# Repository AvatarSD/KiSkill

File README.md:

# KiSkill — agent skills for KiCad

**Give your coding agent full, headless control of any KiCad project.**
KiSkill is a pack of [Claude Code](https://claude.com/claude-code) skills plus
a pure-Python engine (`kx`) that lets an agent read, edit, verify, review, and
fabricate KiCad schematics and PCBs — no GUI, no mouse, every change checked
before it lands.

Built on a lossless s-expression parser (byte-identical round-trips on real
2 MB boards), a geometric verifier that runs before every write, and visual
diffs fed back to the agent so it can *see* what it changed.

> Targets KiCad 9/10 (file-based), plus LIVE board editing in an open KiCad 10
> PCB editor over IPC (`kx live pcb`, also on a remote host via an ssh socket
> forward); live schematic editing rides the same adapter on KiCad 11. On
> KiCad 10 a GENERATED schematic updates in the operator's open editor
> (`kx live sch regen`: save, regenerate, revert through the editor window). The core
> engine is stdlib-only; live mode needs `kicad-python` in the repo `.venv`
> (`python3 -m venv .venv && .venv/bin/pip install kicad-python==0.8.0`).

---

## Install

**Tell your agent** (Claude Code, or any agent that reads `~/.claude/skills/`):

> Clone https://github.com/AvatarSD/KiSkill and run its `install.sh` to set up
> the KiCad skills, then verify with `kx root`.

**Or do it yourself** — one clone, one script, no pip:

```bash
git clone https://github.com/AvatarSD/KiSkill.git
cd KiSkill
./install.sh          # symlinks skills → ~/.claude/skills, kx → ~/.local/bin
```

`install.sh` is idempotent (re-run after `git pull`) and reversible
(`./install.sh --uninstall`). The engine is pure Python stdlib, so there's
nothing to compile. KiCad itself (for ERC / render / fab) is resolved
automatically: native `kicad-cli` on PATH first, then the `org.kicad.KiCad`
flatpak, then the nightly. Override with `KX_KICAD_CLI` — e.g. set it to
`kicad-cli-nightly` when you edit with the v11 nightly, so verification
evidence comes from the same engine that writes your files.

Then just ask:

> *"Use the kicad-project skill to open `~/boards/widget/widget.kicad_pro`,
> add a 3V3 LDO block to the schematic, and show me a diff."*

---

## The skills

| skill              | what it does |
|--------------------|--------------|
| **kicad-project**  | Session state machine (CLEAN→PROBED→…→COMMITTED), backend/lock detection, lib tables, git hygiene. Start here. |
| **kicad-component**| Find parts in local + official libs; fetch missing ones (LCSC via easyeda2kicad, SnapEDA/UltraLibrarian zips); register lib tables. |
| **kicad-schematic**| Generate & edit `.kicad_sch`/`.kicad_pcb` programmatically with a geometric verifier, headless ERC, and rendered visual checks. |
| **kicad-pcb**      | Stage footprints so *Update-PCB-from-Schematic* adopts them without dupes; probe geometry; run DRC; render layers. |
| **kicad-layout**   | Schematic → placed + routed board via freerouting (DSN/SES loop), gated on DRC. |
| **kicad-review**   | Pixel diff, semantic tree diff, ERC/DRC set-diff vs a baseline, and a forum-distilled rule canon. Run before every commit. |
| **kicad-fab**      | Grouped engineering BOM, JLCPCB BOM + CPL, gerbers, drill — ready for the fab house. |
| **kicad-emsim**    | Electromagnetic field sim via gerber2ems + openEMS (dockerized): S-parameters, impedance, E-field PNGs. |
| **kicad-improve**  | Self-improvement loop: each tick researches forums, tests against fixtures, and folds lessons back into the skills. |

Every skill is one self-contained `SKILL.md`. The shared engine lives in
`kicad_lib/` and is reachable from anywhere via the `kx` CLI (`kx root` prints
the repo so skills stay portable no matter where you cloned).

## Why it's safe to let an agent drive

- **Lossless parser** — token-equal round-trips proven on multi-MB boards;
  byte-identical for `.kicad_sch`/`.kicad_sym`/`.kicad_mod`.
- **Verify-before-write** — a geometric verifier (pins, overlaps, grid) must
  pass before any file is saved; nothing commits until a review diff is judged.
- **Evidence, not vibes** — renders and triple diffs flow back to the agent so
  decisions are made on what actually changed.

See [`doc/DESIGN.md`](doc/DESIGN.md) for the architecture, state machine, and
the distilled schematic rule canon.

## Requirements

- Python 3.10+ (engine is stdlib-only).
- KiCad 9 or 10 — native or flatpak (auto-resolved; `KX_KICAD_CLI` to pin) —
  for ERC, rendering, and fab output. Pure file parsing/editing works
  without it.
- Optional per-skill: `cairosvg`/Pillow (render crops), Docker (emsim),
  a bundled freerouting jar (layout).

## Contributing

Issues, fixtures, and PRs welcome — especially real-world boards that stress
the parser and forum-sourced rules worth encoding. Start with
[CONTRIBUTING.md](CONTRIBUTING.md) and the open items in
[`doc/BACKLOG.md`](doc/BACKLOG.md). The `kicad-improve` skill is itself a
working example of how the pack grows.

## License

[MIT](LICENSE) © KiSkill contributors.

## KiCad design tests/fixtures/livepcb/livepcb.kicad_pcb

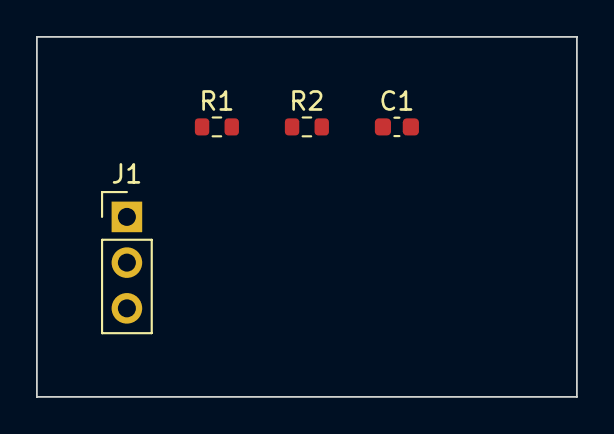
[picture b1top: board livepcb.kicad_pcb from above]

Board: 2 copper layers, 30.0 x 20.0 mm, 4 parts (0 on the bottom side), 3 nets, no tracks yet.

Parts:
C1: 100n; C_0603_1608Metric
J1: IN; PinHeader_1x03_P2.54mm_Vertical
R1, R2: 10k; R_0603_1608Metric

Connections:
GND: C1.2, J1.3, R2.2
OUT: C1.1, J1.2, R1.2, R2.1
VIN: J1.1, R1.1

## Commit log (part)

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2026-06-10 docs: architecture, state machine, atomic ops, rule canon
2026-06-10 feat: lossless sexp parser + round-trip soak test (token-equal on 2.3MB pcb)
2026-06-10 feat: kx CLI — probe (structured schematic inventory) + check
2026-06-10 feat: skill pack v1 — project/component/review/improve + evolved schematic skill + backlog
2026-06-10 fix(skills): subagent-found gaps - flatpak-safe scratch path, lock-file tilde note, deferred-tool note, round-trip claim precision
2026-06-10 docs: tick backlog (geom/verify ported); point skill at kicad_lib.verify
2026-06-10 feat: geom.py — grid snap, rot_xy/mirror, pin world position
2026-06-10 feat: verify.py — geometric verifier (rules 1-6) + mutation tests (8/8 caught)
2026-06-10 fix(verify): coincident pin stacks count as one junction item (eeschema draws no junction at pin-on-pin)
2026-06-10 feat: testproj fixture — generated opamp-follower sheet, verifier-gated, ERC 0/0, visually reviewed
2026-06-10 docs: tick backlog (testproj); skill lesson — place and tie off unused multi-unit opamps
2026-06-10 refactor: gen_testproj drives kicad_lib.ops; test_ops with regen probe-equal gate (caught dropped R2)
2026-06-10 docs: tick backlog (atomic ops at lib level; CLI surface follow-up)
2026-06-10 feat: build.py node builders + ops.py atomic document ops (place/wire/label/junction/set_prop/delete)
2026-06-10 feat: diff.py triple diff (pixel/semantic/ERC) + kx diff REV FILE; alpha-flatten fix for transparent renders
2026-06-10 docs: tick backlog (diff.py); kicad-review skill points at kx diff + transparency gotcha
2026-06-10 feat(sexp): eeschema pts xy-grouping — byte-identical sch/sym/mod round-trip, gated in tests
2026-06-10 fix: regenerate testproj fixture with byte-stable formatter (gate caught stale pts layout)
2026-06-10 feat: component index — sqlite FTS5 over 222 official libs, kx index/find, extends-inheritance
2026-06-10 feat: source.py — kx fetch (easyeda2kicad, live-tested C25804) + import-zip + lib-table registration; sexp order-preservation fix for third-party files
2026-06-10 feat: live.py backend adapter + kx env (locks, IPC socket probe incl. flatpak path, kipy via venv)
2026-06-11 feat: pcb.py footprint staging + kicad-pcb skill (netlist link, uuid refresh, donor empty board)
2026-06-11 feat: fab.py + kicad-fab skill — grouped BOM, JLC BOM/CPL, gerbers+drill via kx fab
2026-06-11 feat: layout.py headless autoroute chain (pcbnew DSN/SES + bundled freerouting) + kicad-layout skill
2026-06-11 feat: emsim.py (gerber2ems+openEMS docker runner, stackup translation) + kicad-emsim skill
2026-06-11 fix(emsim): synthesize default 2-layer FR-4 stackup when board has no (stackup) section
2026-06-11 fix(emsim): mount sim dir at subpath - mounting over /home/docker shadowed the image toolchain
2026-06-11 test+docs: emsim prepare() tests; chain validated via meander_loose smoke (physical S11, 455ps delay)
2026-06-11 fix: e2e sweep #2 — kx wrapper on PATH, nightly-aware env detection, freerouting version glob, donor override, 12 skill-doc gaps closed
2026-06-11 fix(live): real nightly detection — wrapper CLI, 10.99→v11 major, ApiError-tolerant ping, open_documents()
2026-06-11 feat(live): schematic IPC validated on nightly 10.99 — kipy-master bootstrap (protoc+protol+.pth), live read/create/commit/remove e2e test, handler-gap map
2026-06-11 docs(skills): live-IPC editing pattern + handler map into kicad-schematic/kicad-project/DESIGN; env-aware recommended-backend test
2026-06-11 feat(live): kx live — verified atomic ops on the running schematic (wire/junction/label/text/rm, net-blind verifier gate, refusal=no-commit)
2026-06-11 docs(skills): kx live command surface + net-blind gate scope into kicad-schematic; backlog tick
2026-06-11 chore: untrack stray __pycache__
2026-06-11 feat(sexp): .kicad_pcb byte-fidelity — pcb pts dialect (≤5 inline, 4/line chunks) + prettifier token wrap at col 72; real-board soak gate in test_roundtrip
2026-06-11 docs: byte-fidelity now covers pcb — skill warning lifted, backlog tick
2026-06-11 feat(cli): kx power-audit — PWR_FLAG/rail driver sanity from probe; test locks the netlist-drops-PWR_FLAG gotcha (ERC sees it, netlist blind)
2026-06-11 docs(skills): power_pin_not_driven fix recipe + netlist-blind gotcha into kicad-schematic/kicad-review; forum-sweep 1 logged
2026-06-11 feat(cli): kx unit-audit — multi-unit part completeness from the schematic
    Forum sweep 2 (kicad.info unused-pin threads + KLC S4.5): every unit of a
    multi-unit part (dual/quad opamp, gate pack) must be placed, and a spare
    unit still has to be tied off — KiCad ERC raises missing_unit /
    missing_input_pin otherwise. The testproj MCP6002 is a dual opamp (units
    A/B/power, all placed), so the lesson is lockable cold from the existing
    fixture with zero new fixtures.
2026-06-11 docs(skills): multi-unit completeness recipe + kx unit-audit into kicad-schematic/kicad-review; forum-sweep 2 logged
    Deepen the thin missing_unit one-liner in both skills into a recipe: place
    every unit, tie off spares, kx unit-audit front-runs ERC. Log forum-sweep 2
    and the no-connect-discipline candidate for the next sweep.
2026-06-11 test(nc): lock no_connect_connected — NC flag on a live node is an ERC error
    Forum sweep 3 (kicad.info t/46229, t/21294): a No-Connect flag means
    "nothing else attaches here". The inverse trap — a NC flag on a pin/node
    that IS connected — raises `no_connect_connected` (underscores; verified
    empirically, not assumed). Lock it cold from the existing fixture: the clean
    testproj has zero NC markers and no such code; inject one NC on a live
    junction (>=3 segments meet there, so it is unambiguously connected) and the
2026-06-11 docs(skills): no-connect-flag discipline into kicad-schematic/kicad-review; forum-sweep 3 logged
    Both directions: add a NC flag to a genuinely-unused pin to silence
    pin_not_connected (document intent, don't lower severity); the inverse trap
    no_connect_connected = a NC flag on a wired node (delete flag or wire, not
    both). Log sweep 3 and queue reference annotation/uniqueness as the next
    unblocked candidate (completes the power/unit/reference pre-flight trio).
2026-06-11 feat(cli): kx ref-audit — reference uniqueness/annotation (ERC is blind to it)
    Forum sweep 4 (kicad.info t/32585 + Annotation docs) completes the
    power/unit/reference pre-flight trio. PROVEN gotcha (not assumed): kicad-cli
    sch erc --severity-all reports 0/0 for both a duplicate designator (two R1)
    and an unannotated one (R?) — duplicate-ref and annotation are Annotation-
    tool checks (SCH_REFERENCE_LIST), NOT ERC violations. A headless ERC pass
    stays green while two R1s cross-merge in the netlist. Parallel to the
2026-06-11 docs(skills): ERC is blind to dup/unannotated refs + kx ref-audit; forum-sweep 4 logged
    Add the proven gotcha (kicad-cli sch erc does NOT catch duplicate or
    unannotated designators — annotation-tool checks, not ERC) to kicad-schematic
    §7 and a new "what headless ERC does NOT catch" block in kicad-review, both
    pointing at kx ref-audit. Log sweep 4 (pre-flight trio complete) and queue
    default-disabled ERC checks (the .rpt "Ignored checks" footer) as next.
2026-06-11 docs(backlog): reliability gap audit — 9 prioritized items from code analysis
    Audit of kicad_lib + kx + skills for what blocks RELIABLE agent edits:
    1. verify() never runs against the file on disk (only live_ops/tests) —
    netmodel extraction is the keystone item; unblocks the sweep-3 NC
    audit and 'netlist == intent'.
    2. No kx write-op CLI — file edits lack the live_ops refusal contract.
    3. flatpak invocation hardcoded in diff/fab/pcb/emsim + index OFFICIAL
2026-06-11 feat(kcli): one kicad-cli resolver — evidence engine must match editing engine
    Found live: user edits with the native v11 nightly while diff/fab/pcb/
    live each hardcoded the flatpak KiCad 10 — ERC/render/netlist evidence
    came from a DIFFERENT engine than the one writing the files.
    - kcli.py: cmd() = KX_KICAD_CLI env (shlex) → native kicad-cli on PATH →
    flatpak → kicad-cli-nightly; symbols_dir() mirrors the preference
    (KX_KICAD_SYMBOLS override, native /usr/share/kicad/symbols fallback).
